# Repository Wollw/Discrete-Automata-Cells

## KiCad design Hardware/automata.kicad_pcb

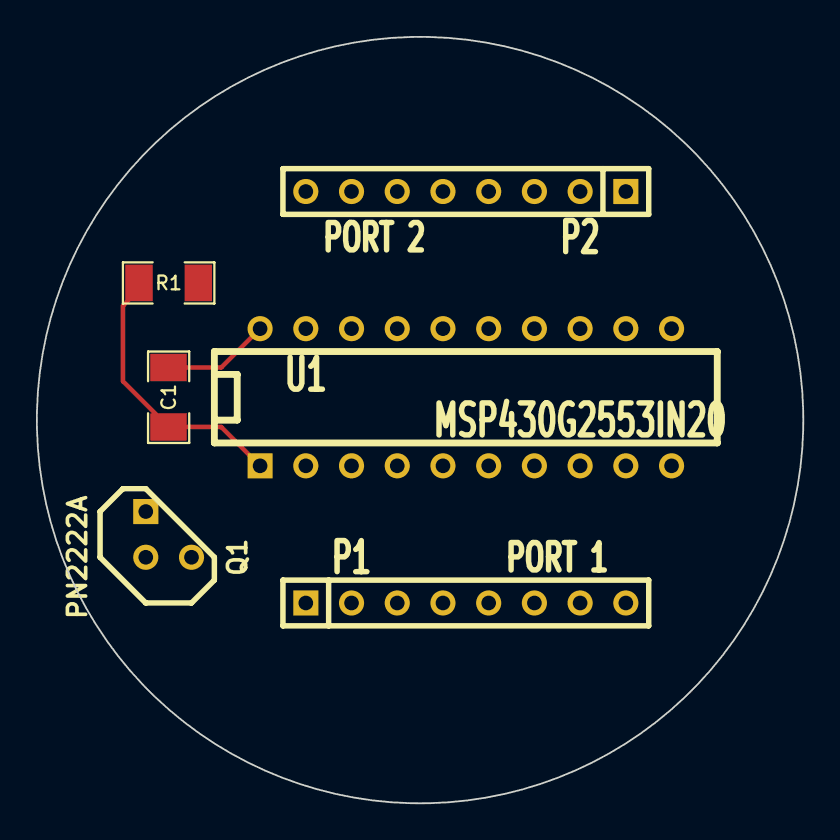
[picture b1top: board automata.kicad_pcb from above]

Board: 2 copper layers, 42.6 x 42.6 mm, 6 parts (0 on the bottom side), 19 nets.

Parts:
C1: 0.1uF; SM1206
P1: PORT 1; SIL-8
P2: PORT 2; SIL-8
Q1: PN2222A; TO92-123
R1: 47k; SM1206
U1: MSP430G2553IN20; DIP-20__300

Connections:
/P1.0: P1.1, Q1.2, U1.2
/P1.1: P1.2, U1.3
/P1.2: P1.3, U1.4
/P1.3: P1.4, U1.5
/P1.4: P1.5, U1.6
/P1.5: P1.6, U1.7
/P1.6: P1.7, U1.14
/P1.7: P1.8, U1.15
/P2.0: P2.1, U1.8
/P2.1: P2.2, U1.9
/P2.2: P2.3, U1.10
/P2.3: P2.4, U1.11
/P2.4: P2.5, U1.12
/P2.5: P2.6, U1.13
/P2.6: P2.7, U1.19
/P2.7: P2.8, U1.18
/RST: R1.2, U1.16
GND: C1.2, U1.20
VCC: C1.1, R1.1, U1.1

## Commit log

2014-04-14 Fixed some bugs a
2014-04-14 change to c99 instead of gnu99
2014-04-14 added -Werror
2014-04-14 Added Hardware and Firmware directories
2014-04-14 changed mcu
2014-04-15 Started developing schematic and circuit board.
2014-04-18 fixed bug causing firmware not to function
2014-04-18 previous fix wasn't enough, this should make things work more reliably
2014-05-20 moved neighbor state reading before wait for falling edge on clock. the wait is intended to hold cells back until all cells finish reading states, thus if they read states after the wait it does noth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
2014-06-04 Added proposal
2014-06-04 Finished draft of writeup for 147
2014-07-09 removed proposal
